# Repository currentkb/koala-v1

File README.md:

# koala keyboard

This is a 34-key column-staggered unibody keyboard.

## PCB

You can modify the [KiCad files](/kicad/) or straight download the [Gerber files](/gerber/) to order the PCB.

## BUILD GUIDE
  
The build guide for the koala can be found [here](/docs/buildguide.md).
## Firmware

### QWERTY
      ┌───┬───┬───┬───┬───┐   ┌───┬───┬───┬───┬───┐
      │ Q │ W │ E │ R │ T │   │ Y │ U │ I │ O │ P │
      ├───┼───┼───┼───┼───│   │───┼───┼───┼───┼───┤
      │ A │ S │ D │ F │ G │   │ H │ J │ K │ L │ ; │
      ├───┼───┼───┼───┼───│   │───┼───┼───┼───┼───┤
      │ Z │ X │ C │ V │ B │   │ N │ M │ , │ . │ / │
      └───┴───┴───┼───┼───│   │───┼───┼───┴───┴───┘
                  │Ent│Tab│   │Bsp│Spc│
                  └───┴───┘   └───┴───┘
[QMK config: QWERTY](https://github.com/currentkb/qmk_firmware/tree/feat/koala/keyboards/koala/keymaps/default)

[pre-built firmware: QWERTY](/firmware/koala_default.hex)
### COLEMAK DH
    
      ┌───┬───┬───┬───┬───┐   ┌───┬───┬───┬───┬───┐
      │ Q │ W │ F │ P │ B │   │ J │ L │ U │ Y │ ; │
      ├───┼───┼───┼───┼───│   │───┼───┼───┼───┼───┤
      │ A │ R │ S │ T │ G │   │ M │ N │ E │ I │ O │
      ├───┼───┼───┼───┼───│   │───┼───┼───┼───┼───┤
      │ Z │ X │ C │ D │ V │   │ K │ H │ , │ . │ / │
      └───┴───┴───┼───┼───│   │───┼───┼───┴───┴───┘
                  │Ent│Tab│   │Bsp│Spc│
                  └───┴───┘   └───┴───┘

[QMK config: COLEMAK DH](https://github.com/currentkb/qmk_firmware/tree/feat/koala/keyboards/koala/keymaps/colemakdh)

[pre-built firmware: COLEMAK DH](/firmware/koala_colemakdh.hex)

## CREDITS

### INSPIRATION

The keyboard is inspired by the [clog-v4 keyboard from smores](https://github.com/smores56/clog-v4).

[Sam Mohr](https://github.com/smores56)

### PROCESS

The keyboard was built with the use of the [tutorial of FlatFootFox](https://flatfootfox.com/ergogen-introduction/).

[FlatFootFox](https://flatfootfox.com/)

### DOCUMENTATION

I used the [repository of the TOTEM keyboard](https://github.com/GEIGEIGEIST/TOTEM) as a reference to build this.

[GEIST](https://github.com/GEIGEIGEIST)

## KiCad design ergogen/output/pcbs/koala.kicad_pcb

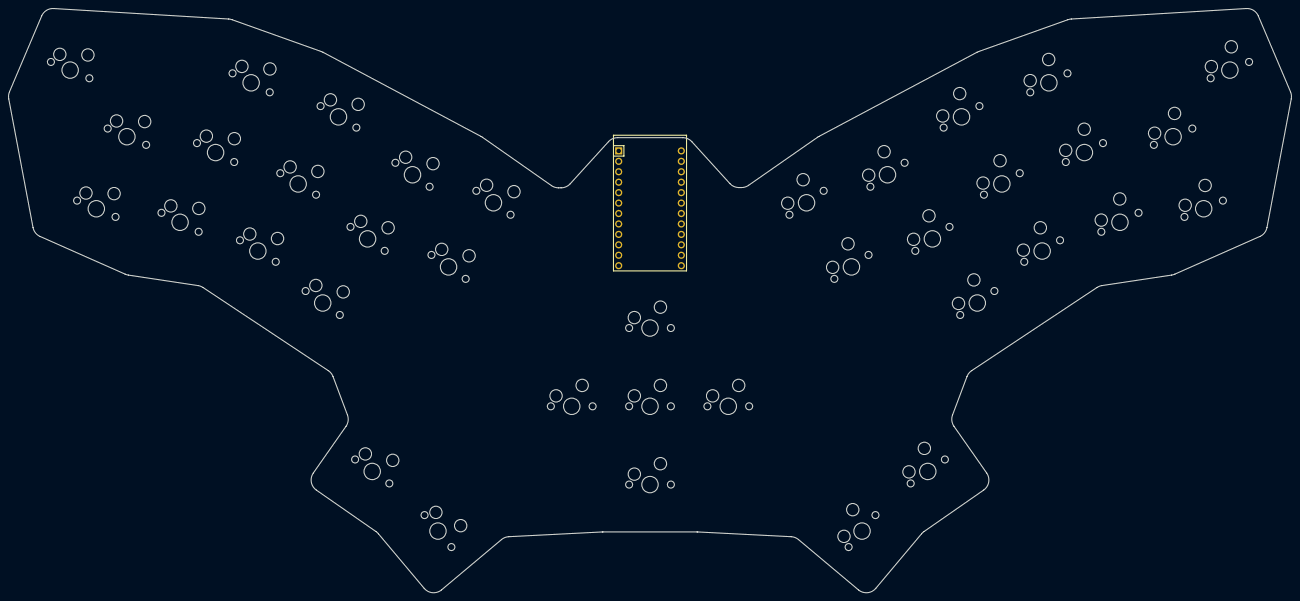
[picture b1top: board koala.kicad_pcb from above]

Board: 2 copper layers, 312.2 x 142.2 mm, 75 parts (0 on the bottom side), 52 nets, no tracks yet.

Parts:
D1, D2, D3, D4, D5, D6, D7, D8, D9, D10, D11, D12, D13, D14, D15, D16, D17, D18, D19, D20, D21, D22, D23, D24, D25, D26, D27, D28, D29, D30, D31, D32, D33, D34, D35, D36, D37: D_SOD123
MCU1: ProMicro
S1, S2, S3, S4, S5, S6, S7, S8, S9, S10, S11, S12, S13, S14, S15, S16, S17, S18, S19, S20, S21, S22, S23, S24, S25, S26, S27, S28, S29, S30, S31, S32, S33, S34, S35, S36, S37: MX

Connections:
GND: MCU1.2, MCU1.15, MCU1.16
P2: MCU1.17, S22.1, S23.1, S24.1
P3: MCU1.18, S25.1, S26.1, S27.1
P4: MCU1.19, S28.1, S29.1, S30.1
P5: MCU1.20, S31.1, S32.1, S33.1, S36.1
P6: MCU1.21, S34.1, S35.1, S37.1
P8: D2.1, D5.1, D8.1, D11.1, D13.1, D23.1, D26.1, D29.1, D32.1, D34.1, MCU1.23
P9: D15.1, D16.1, D36.1, D37.1, MCU1.24
P10: D1.1, D4.1, D7.1, D10.1, D22.1, D25.1, D28.1, D31.1, MCU1.12
P15: MCU1.9, S13.1, S14.1, S16.1
P16: D3.1, D6.1, D9.1, D12.1, D14.1, D24.1, D27.1, D30.1, D33.1, D35.1, MCU1.11
P18: MCU1.8, S10.1, S11.1, S12.1, S15.1
P19: MCU1.7, S7.1, S8.1, S9.1
P20: MCU1.6, S4.1, S5.1, S6.1
P21: MCU1.5, S1.1, S2.1, S3.1
center_down: D18.2, S18.2
center_middle: D19.2, S19.2
center_up: D20.2, S20.2
index_bottom: D10.2, S10.2
index_home: D11.2, S11.2
index_top: D12.2, S12.2
inner_cluster: D15.2, S15.2
inner_home: D13.2, S13.2
inner_top: D14.2, S14.2
left_middle: D17.2, S17.2
middle_bottom: D7.2, S7.2
middle_home: D8.2, S8.2
middle_top: D9.2, S9.2
mirror_index_bottom: D31.2, S31.2
mirror_index_home: D32.2, S32.2
mirror_index_top: D33.2, S33.2
mirror_inner_cluster: D36.2, S36.2
mirror_inner_home: D34.2, S34.2
mirror_inner_top: D35.2, S35.2
mirror_middle_bottom: D28.2, S28.2
mirror_middle_home: D29.2, S29.2
mirror_middle_top: D30.2, S30.2
mirror_outer_cluster: D37.2, S37.2
mirror_pinky_bottom: D22.2, S22.2
mirror_pinky_home: D23.2, S23.2
mirror_pinky_top: D24.2, S24.2
mirror_ring_bottom: D25.2, S25.2
mirror_ring_home: D26.2, S26.2
mirror_ring_top: D27.2, S27.2
outer_cluster: D16.2, S16.2
pinky_bottom: D1.2, S1.2
pinky_home: D2.2, S2.2
pinky_top: D3.2, S3.2
right_middle: D21.2, S21.2
ring_bottom: D4.2, S4.2
ring_home: D5.2, S5.2
ring_top: D6.2, S6.2

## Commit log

2023-04-10 feat(): initial commit
2023-04-10 doc(): add missing info
2023-04-10 chore(): add drill files and update production
2023-04-23 feat(): add documentation and firmware
2023-04-28 create new keyboard
